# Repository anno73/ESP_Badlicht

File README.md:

# Work in progress

# ESP_Badlicht

ESP8266 based project to control several LED RGB light strips via multiple PCA9685.

Uses [IotWebConf](https://github.com/prampec/IotWebConf).

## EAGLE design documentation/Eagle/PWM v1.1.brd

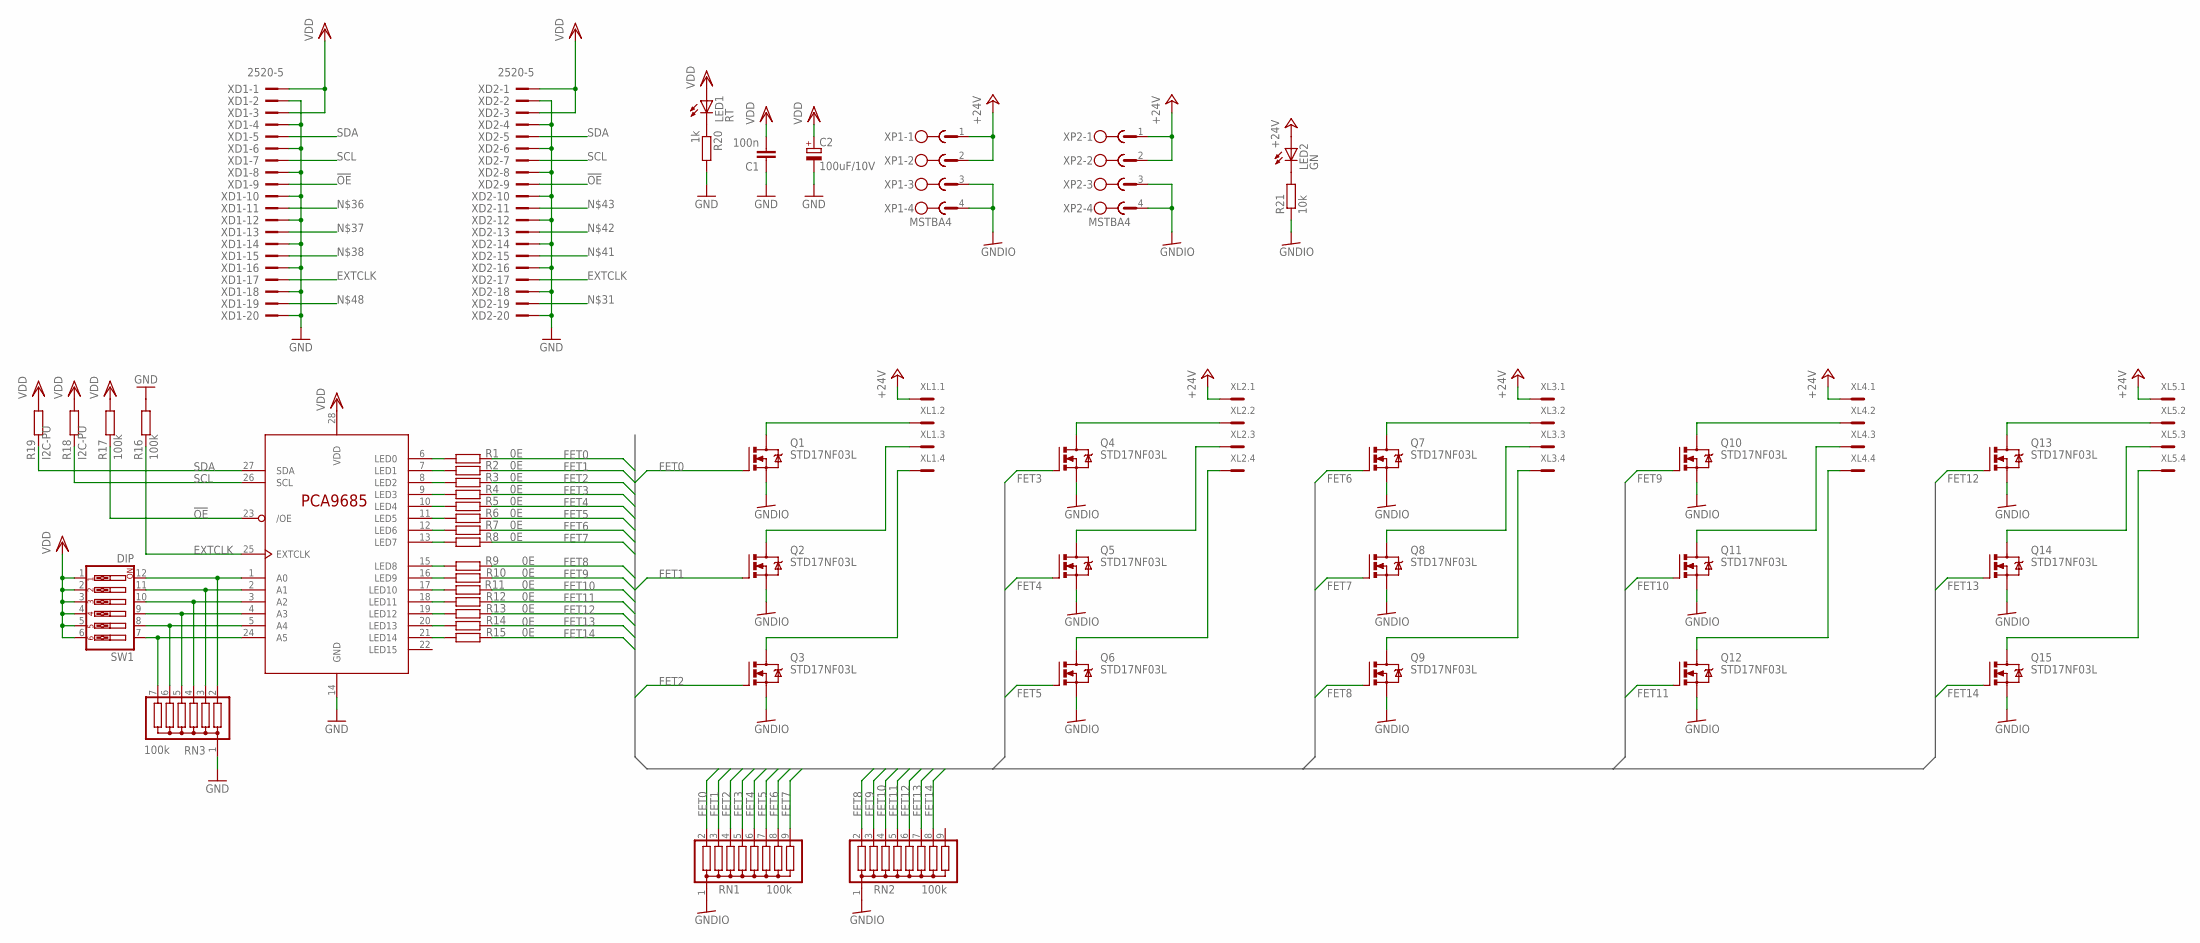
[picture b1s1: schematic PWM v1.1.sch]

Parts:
C1: 100n; C025_050-035X075
C2: 100uF/10V; E5-10,5
IC1: PCA9685; DIL28-6
LED1: RT; LED3MM
LED2: GN; LED3MM
Q1, Q2, Q3, Q4, Q5, Q6, Q7, Q8, Q9, Q10, Q11, Q12, Q13, Q14, Q15: STD17NF03L; TO251AA-V
R1, R2, R3, R4, R5, R6, R7, R8, R9, R10, R11, R12, R13, R14, R15: 0E; 0207/2V
R16, R17: 100k; 0207/2V
R18, R19: I2C-PU; 0207/2V
R20: 1k; 0207/2V
R21: 10k; 0207/2V
RN1, RN2: 100k; SIL9
RN3: 100k; SIL7
SW1: DIP; EDG-06
XD1, XD2: 2520-5; PAK100/2500-5-20
XL1, XL2, XL3, XL4, XL5: MC4
XP1, XP2: MSTBA4

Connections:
!OE: IC1.23 (/OE), R17.2, XD1.9, XD2.9
+24V: LED2.A, XL1.1, XL2.1, XL3.1, XL4.1, XL5.1, XP1.1, XP1.2, XP2.1, XP2.2
EXTCLK: IC1.25 (EXTCLK), R16.1, XD1.17, XD2.17
FET0: Q1.1 (G), R1.1, RN1.9
FET1: Q2.1 (G), R2.2, RN1.8
FET2: Q3.1 (G), R3.1, RN1.7
FET3: Q4.1 (G), R4.2, RN1.6
FET4: Q5.1 (G), R5.1, RN1.5
FET5: Q6.1 (G), R6.2, RN1.4
FET6: Q7.1 (G), R7.1, RN1.3
FET7: Q8.1 (G), R8.2, RN1.2
FET8: Q9.1 (G), R9.2, RN2.2
FET9: Q10.1 (G), R10.1, RN2.3
FET10: Q11.1 (G), R11.2, RN2.4
FET11: Q12.1 (G), R12.1, RN2.5
FET12: Q13.1 (G), R13.2, RN2.6
FET13: Q14.1 (G), R14.1, RN2.7
FET14: Q15.1 (G), R15.2, RN2.8
GND: C1.1, C2.-, IC1.14 (GND), R16.2, R20.2, RN3.1, XD1.2, XD1.4, XD1.6, XD1.8, XD1.10, XD1.12, XD1.14, XD1.16, XD1.18, XD1.20, XD2.2, XD2.4, XD2.6, XD2.8, XD2.10, XD2.12, XD2.14, XD2.16, XD2.18, XD2.20
GNDIO: Q1.3 (S), Q2.3 (S), Q3.3 (S), Q4.3 (S), Q5.3 (S), Q6.3 (S), Q7.3 (S), Q8.3 (S), Q9.3 (S), Q10.3 (S), Q11.3 (S), Q12.3 (S), Q13.3 (S), Q14.3 (S), Q15.3 (S), R21.1, RN1.1, RN2.1, XP1.3, XP1.4, XP2.3, XP2.4
unnamed: Q1.2 (D), XL1.2
unnamed: Q2.2 (D), XL1.3
unnamed: Q3.2 (D), XL1.4
unnamed: Q6.2 (D), XL2.4
unnamed: Q4.2 (D), XL2.2
unnamed: Q5.2 (D), XL2.3
unnamed: Q8.2 (D), XL3.3
unnamed: Q7.2 (D), XL3.2
unnamed: Q9.2 (D), XL3.4
unnamed: Q10.2 (D), XL4.2
unnamed: Q11.2 (D), XL4.3
unnamed: Q12.2 (D), XL4.4
unnamed: Q13.2 (D), XL5.2
unnamed: Q14.2 (D), XL5.3
unnamed: Q15.2 (D), XL5.4
unnamed: IC1.6 (LED0), R1.2
unnamed: IC1.7 (LED1), R2.1
unnamed: IC1.8 (LED2), R3.2
unnamed: IC1.9 (LED3), R4.1
unnamed: IC1.10 (LED4), R5.2
unnamed: IC1.11 (LED5), R6.1
unnamed: IC1.12 (LED6), R7.2
unnamed: IC1.13 (LED7), R8.1
unnamed: IC1.15 (LED8), R9.1
unnamed: IC1.16 (LED9), R10.2
unnamed: IC1.17 (LED10), R11.1
unnamed: IC1.18 (LED11), R12.2
unnamed: IC1.19 (LED12), R13.1
unnamed: IC1.20 (LED13), R14.2
unnamed: IC1.21 (LED14), R15.1
unnamed: IC1.1 (A0), RN3.2, SW1.12
unnamed: IC1.2 (A1), RN3.3, SW1.11
unnamed: IC1.3 (A2), RN3.4, SW1.10
unnamed: IC1.4 (A3), RN3.5, SW1.9
unnamed: IC1.5 (A4), RN3.6, SW1.8
unnamed: IC1.24 (A5), RN3.7, SW1.7
unnamed: LED1.K (C), R20.1
unnamed: LED2.K (C), R21.2
SCL: IC1.26 (SCL), R18.2, XD1.7, XD2.7
SDA: IC1.27 (SDA), R19.1, XD1.5, XD2.5
VDD: C1.2, C2.+, IC1.28 (VDD), LED1.A, R17.1, R18.1, R19.2, SW1.1, SW1.2, SW1.3, SW1.4, SW1.5, SW1.6, XD1.1, XD1.3, XD2.1, XD2.3

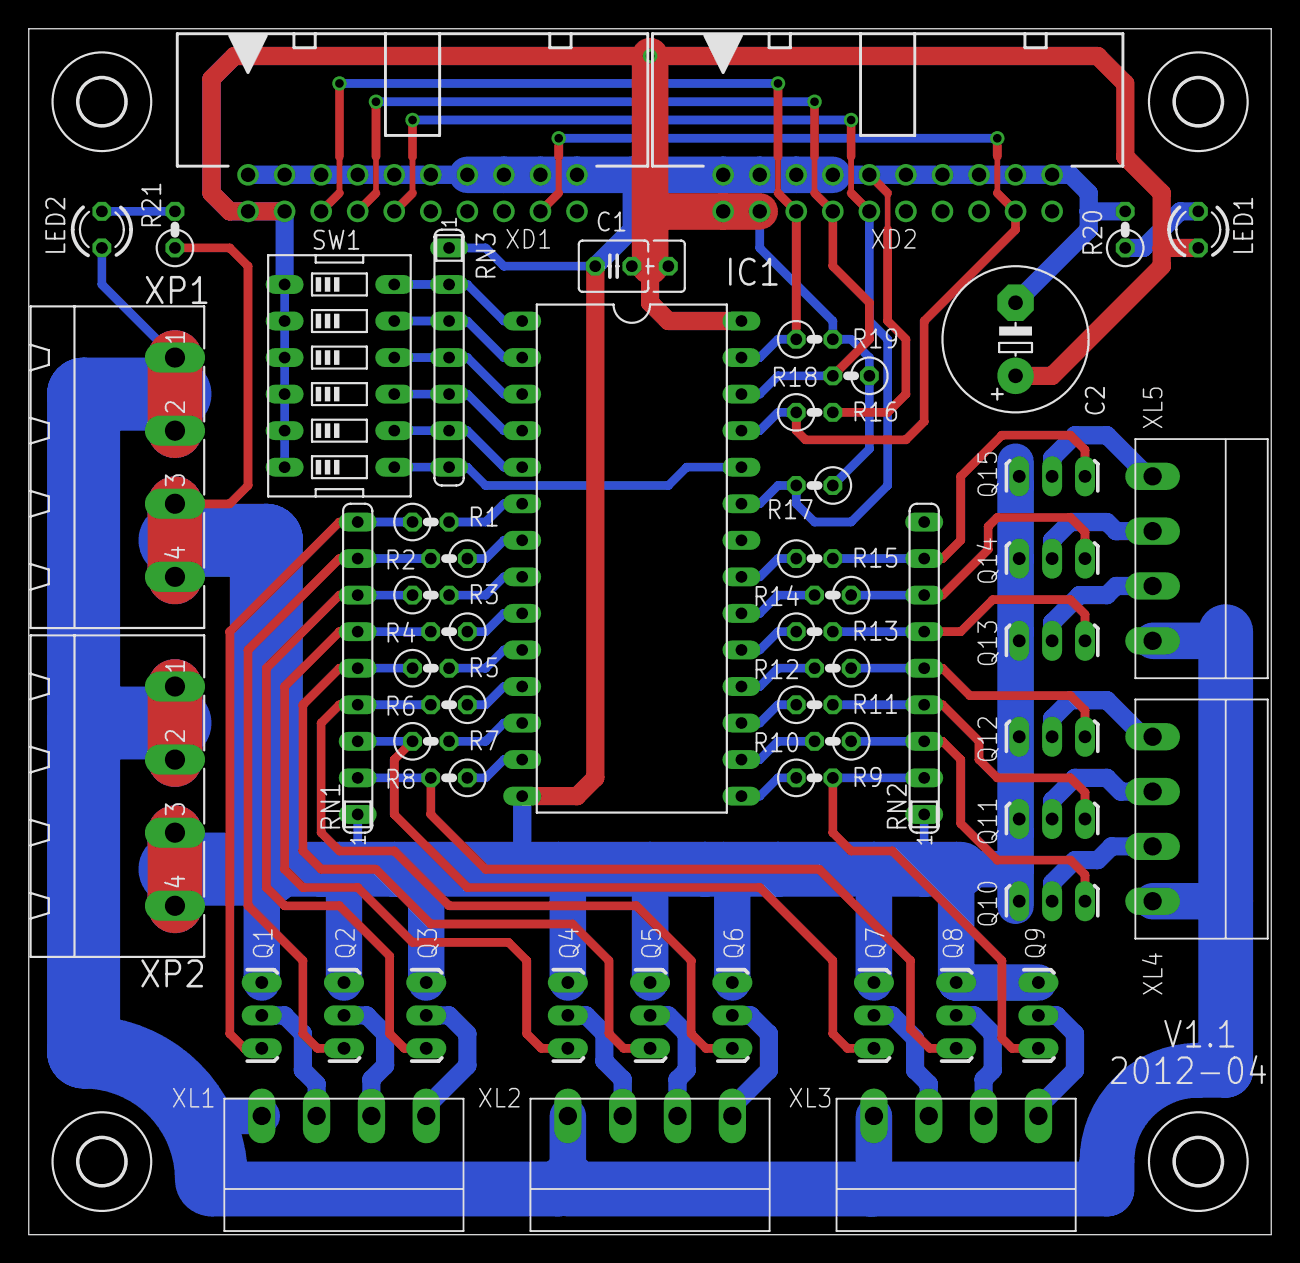
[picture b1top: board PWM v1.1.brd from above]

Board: 2 copper layers, 86.3 x 83.8 mm, 58 parts (0 on the bottom side), 61 nets.

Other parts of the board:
U$1, U$2, U$3, U$4: 3,2

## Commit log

2020-12-17 Initial
2020-12-17 Compiles in Arduino 1.8.13
2020-12-18 change src dir for better Arduino compatibility
2020-12-19 convert from ino to cpp - IotWebConf not working
2020-12-19 Major restructure. Finally compiles.
2020-12-19 Some code cleanup
2020-12-29 Move OTA to own namespace
2020-12-30 minor update
2020-12-30 MQTT command structure, stub I2C, convert defines
2020-12-30 Schematic and PCB
2020-12-30 Docu
2020-12-30 Cleanup
2020-12-30 #pragma once
2020-12-31 updates, fixes, enhancements
2020-12-31 Fix serializeJson append
2020-12-31 Switch to native time support
2020-12-31 config monitor_port
2021-01-01 convert #define to const
2021-01-01 point to version 3.0.0
2021-01-01 fix typo
2021-01-01 upgrade to iotwebconf 3.0.0 initial commit
2021-01-01 Add more parameters to startpage
2021-01-01 Comment on pwd length
2021-01-15 enable config of mqtt hearbeat intervall
2021-01-15 nail version of IWC
2021-01-31 docu, cleanup
2021-01-31 rename workspace file
2021-02-09 Missing forward declaration of handleRoot()
